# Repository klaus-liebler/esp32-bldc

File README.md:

# esp32-bldc - a bldc controller for stationary applications

* Main components are ESP32-S3, DRV8323HRTAR, 6x IRF7480

* Intgrated synchronous step down converter
* CAN-BUS, RS485 (both with switchable termination)
* USB-C, I2C
* All ceramic capacitors
* Power-LED
* Reset Button, Boot Button
* Thermal sensor
* breakable connector area
* optional MT6816 at the bottom PCB side
* parts available at jlcpcb, (5pcs = 113€)
* various GPIO; especially for external magnetic sensor
* desinged with [KiCad](https://www.kicad.org/) with [https://simplefoc.com/](https://simplefoc.com/) in mind
* Four mounting holes
* dimensions 60mm x 52mm (63mm with big connectors)
* currently COMPLETELY untested

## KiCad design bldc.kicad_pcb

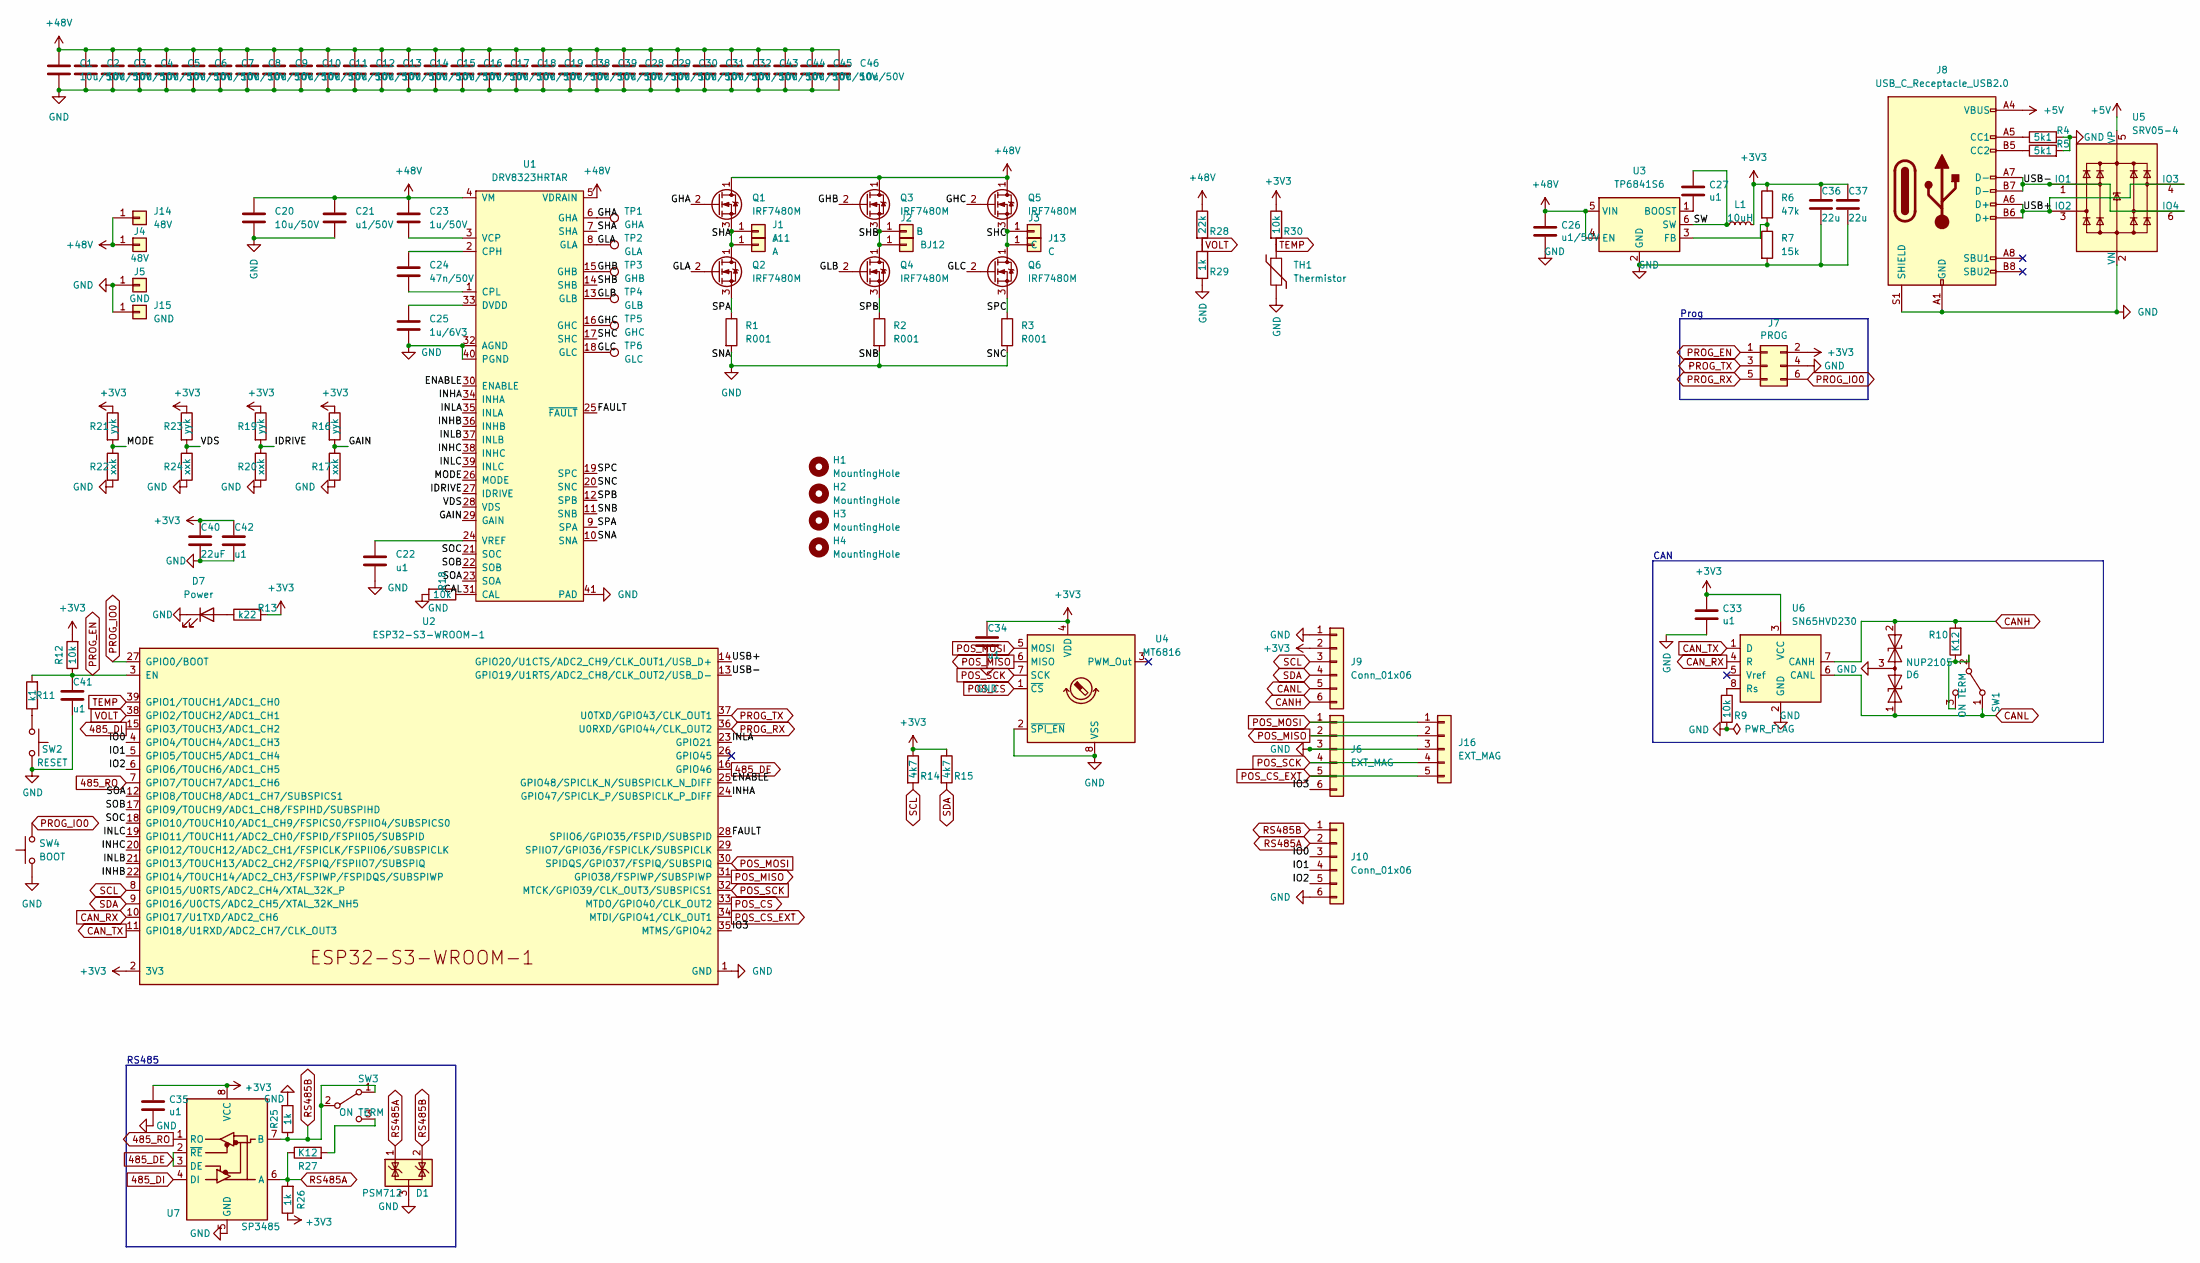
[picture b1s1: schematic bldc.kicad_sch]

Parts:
C1, C2, C3, C4, C5, C6, C7, C8, C9, C10, C11, C12, C13, C14, C15, C16, C17, C18, C19, C28, C29, C30, C31, C32, C38, C39, C43, C44, C45, C46: 10u/50V; C_1206_3216Metric_smaller
C20: 10u/50V; C_1206_3216Metric
C21, C26: u1/50V; C_0603_1608Metric
C22, C27, C33, C35, C41, C42: u1; C_0402_1005Metric
C23: 1u/50V; C_0603_1608Metric
C24: 47n/50V; C_0603_1608Metric
C25: 1u/6V3; C_0402_1005Metric
C34: u1; C_0805_2012Metric_Pad1.18x1.45mm_HandSolder
C36, C37: 22u; C_0603_1608Metric
C40: 22uF; C_0603_1608Metric
D1: PSM712; SOT-23_smaller_withoutSilkscreen
D6: NUP2105; SOT-23_Handsoldering
D7: Power; LED_0603_1608Metric
H1, H2, H3, H4: MountingHole; MountingHole_3.2mm_M3_DIN965
J1: A; SolderWirePad_1x01_SMD_3x5mm
J2: B; SolderWirePad_1x01_SMD_3x5mm
J3: C; SolderWirePad_1x01_SMD_3x5mm
J4: 48V; SolderWirePad_1x01_SMD_3x5mm
J5: GND; SolderWirePad_1x01_SMD_3x5mm
J6: EXT_MAG; JST_XH_S6B-XH-A_1x06_P2.50mm_Horizontal
J7: PROG; IDC_2x03_P1.27mm_Vertical
J8: USB_C_Receptacle_USB2.0; USB_C_Receptacle_HRO_TYPE-C-31-M-12
J9, J10: Conn_01x06; JST_XH_S6B-XH-A_1x06_P2.50mm_Horizontal
J11: A; Steckzunge_4_8mm
J12: B; Steckzunge_4_8mm
J13: C; Steckzunge_4_8mm
J14: 48V; Steckzunge_4_8mm
J15: GND; Steckzunge_4_8mm
J16: EXT_MAG; PhoenixContact_MC_1,5_5-G-3.81_1x05_P3.81mm_Horizontal
L1: 10uH; L_Abracon_ASPI-0630LR
Q1, Q2, Q3, Q4, Q5, Q6: IRF7480M; DirectFET_ME
R1, R2, R3: R001; R_2512_6332Metric
R4, R5: 5k1; R_0402_1005Metric
R6: 47k; R_0402_1005Metric
R7: 15k; R_0402_1005Metric
R9, R12, R18, R30: 10k; R_0402_1005Metric
R10, R27: K12; R_1206_3216Metric_Pad1.30x1.75mm_HandSolder
R11: k1; R_0402_1005Metric
R13: k22; R_0402_1005Metric
R14, R15: 4k7; R_0402_1005Metric
R16, R19, R21, R23: yyk; R_0805_2012Metric_Pad1.20x1.40mm_HandSolder
R17, R20, R22, R24: xxk; R_0805_2012Metric_Pad1.20x1.40mm_HandSolder
R25, R26: 1k; R_0603_1608Metric
R28: 22k; R_0402_1005Metric
R29: 1k; R_0402_1005Metric
SW1, SW3: ON TERM; Switch_SS12D00
SW2: RESET; SW_SPST_TL3342
SW4: BOOT; SW_SPST_TL3342
TH1: Thermistor; R_Axial_DIN0204_L3.6mm_D1.6mm_P1.90mm_Vertical
TP1: GHA; TestPoint_THTPad_D1.0mm_Drill0.5mm
TP2: GLA; TestPoint_THTPad_D1.0mm_Drill0.5mm
TP3: GHB; TestPoint_THTPad_D1.0mm_Drill0.5mm
TP4: GLB; TestPoint_THTPad_D1.0mm_Drill0.5mm
TP5: GHC; TestPoint_THTPad_D1.0mm_Drill0.5mm
TP6: GLC; TestPoint_THTPad_D1.0mm_Drill0.5mm
U1: DRV8323HRTAR; Texas_S-PVQFN-N40_EP4.15x4.15mm_ThermalVias
U2: ESP32-S3-WROOM-1
U3: TP6841S6; TSOT-23-6
U4: MT6816; SO-8_3.9x4.9mm_P1.27mm
U5: SRV05-4; SOT-23-6
U6: SN65HVD230; SOIC-8_3.9x4.9mm_P1.27mm
U7: SP3485; SOIC-8_3.9x4.9mm_P1.27mm

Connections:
485_DE: U2.16 (GPIO46), U7.2 (~RE), U7.3 (DE)
485_DI: U2.15 (GPIO3/TOUCH3/ADC1_CH2), U7.4 (DI)
485_RO: U2.7 (GPIO7/TOUCH7/ADC1_CH6), U7.1 (RO)
+3V3: C33.1, C34.2, C35.2, C36.1, C37.1, C40.1, C42.2, J7.2, J9.2, L1.2, R6.1, R12.2, R13.2, R14.1, R15.1, R16.1, R19.1, R21.1, R23.1, R26.1, R30.1, U2.2 (3V3), U4.4 (VDD), U6.3 (VCC), U7.8 (VCC)
+5V: J8.A4 (VBUS), J8.A9 (VBUS), J8.B4 (VBUS), J8.B9 (VBUS), U5.5 (VP)
+48V: C1.1, C2.1, C3.1, C4.1, C5.1, C6.1, C7.1, C8.1, C9.1, C10.1, C11.1, C12.1, C13.1, C14.1, C15.1, C16.1, C17.1, C18.1, C19.1, C20.2, C21.1, C23.1, C26.1, C28.1, C29.1, C30.1, C31.1, C32.1, C38.1, C39.1, C43.1, C44.1, C45.1, C46.1, J4.1, J14.1, Q1.1 (D), Q3.1 (D), Q5.1 (D), R28.1, U1.4 (VM), U1.5 (VDRAIN), U3.4 (EN), U3.5 (VIN)
/CAL: R18.1, U1.31 (CAL)
/ENABLE: U1.30 (ENABLE), U2.25 (GPIO48/SPICLK_N/SUBSPICLK_N_DIFF)
/FAULT: U1.25 (~FAULT), U2.28 (SPIIO6/GPIO35/FSPID/SUBSPID)
/GAIN: R16.2, R17.1, U1.29 (GAIN)
/GHA: Q1.2 (G), TP1.1, U1.6 (GHA)
/GHB: Q3.2 (G), TP3.1, U1.15 (GHB)
/GHC: Q5.2 (G), TP5.1, U1.16 (GHC)
/GLA: Q2.2 (G), TP2.1, U1.8 (GLA)
/GLB: Q4.2 (G), TP4.1, U1.13 (GLB)
/GLC: Q6.2 (G), TP6.1, U1.18 (GLC)
/IDRIVE: R19.2, R20.1, U1.27 (IDRIVE)
/INHA: U1.34 (INHA), U2.24 (GPIO47/SPICLK_P/SUBSPICLK_P_DIFF)
/INHB: U1.36 (INHB), U2.22 (GPIO14/TOUCH14/ADC2_CH3/FSPIWP/FSPIDQS/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)
/INHC: U1.38 (INHC), U2.20 (GPIO12/TOUCH12/ADC2_CH1/FSPICLK/FSPIIO6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)
/INLA: U1.35 (INLA), U2.23 (GPIO21)
/INLB: U1.37 (INLB), U2.21 (GPIO13/TOUCH13/ADC2_CH2/FSPIQ/FSPIIO7/S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)
/INLC: U1.39 (INLC), U2.19 (GPIO11/TOUCH11/ADC2_CH0/FSPID/FSPIIO5/S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)
/IO0: J10.3, U2.4 (GPIO4/TOUCH4/ADC1_CH3)
/IO1: J10.4, U2.5 (GPIO5/TOUCH5/ADC1_CH4)
/IO2: J10.5, U2.6 (GPIO6/TOUCH6/ADC1_CH5)
/IO3: J6.6, U2.35 (MTMS/GPIO42)
/MODE: R21.2, R22.1, U1.26 (MODE)
/SHA: J1.1, J11.1, Q1.3 (S), Q2.1 (D), U1.7 (SHA)
/SHB: J2.1, J12.1, Q3.3 (S), Q4.1 (D), U1.14 (SHB)
/SHC: J3.1, J13.1, Q5.3 (S), Q6.1 (D), U1.17 (SHC)
/SOA: U1.23 (SOA), U2.12 (GPIO8/TOUCH8/ADC1_CH7/SUBSPICS1)
/SOB: U1.22 (SOB), U2.17 (GPIO9/TOUCH9/ADC1_CH8/FSPIHD/SUBSPIHD)
/SOC: U1.21 (SOC), U2.18 (GPIO10/TOUCH10/ADC1_CH9/FSPICS0/FSPIIO4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)
/SPA: Q2.3 (S), R1.1, U1.9 (SPA)
/SPB: Q4.3 (S), R2.1, U1.12 (SPB)
/SPC: Q6.3 (S), R3.1, U1.19 (SPC)
/SW: C27.1, L1.1, U3.6 (SW)
/USB+: J8.A6 (D+), J8.B6 (D+), U2.14 (GPIO20/U1CTS/ADC2_CH9/CLK_OUT1/USB_D+), U5.3 (IO2), U5.4 (IO3)
/USB-: J8.A7 (D-), J8.B7 (D-), U2.13 (GPIO19/U1RTS/ADC2_CH8/CLK_OUT2/USB_D-), U5.1 (IO1), U5.6 (IO4)
/VDS: R23.2, R24.1, U1.28 (VDS)
CANH: D6.2 (A2), J9.6, R10.2, U6.7 (CANH)
CANL: D6.1 (A1), J9.5, SW1.1 (A), U6.6 (CANL)
CAN_RX: U2.10 (GPIO17/U1TXD/ADC2_CH6), U6.4 (R)
CAN_TX: U2.11 (GPIO18/U1RXD/ADC2_CH7/CLK_OUT3), U6.1 (D)
GND: C1.2, C2.2, C3.2, C4.2, C5.2, C6.2, C7.2, C8.2, C9.2, C10.2, C11.2, C12.2, C13.2, C14.2, C15.2, C16.2, C17.2, C18.2, C19.2, C20.1, C21.2, C22.2, C25.2, C26.2, C28.2, C29.2, C30.2, C31.2, C32.2, C33.2, C34.1, C35.1, C36.2, C37.2, C38.2, C39.2, C40.2, C41.2, C42.1, C43.2, C44.2, C45.2, C46.2, D1.3 (A), D6.3 (common), D7.1 (K), J5.1, J6.3, J7.4, J8.A1 (GND), J8.A12 (GND), J8.B1 (GND), J8.B12 (GND), J8.S1 (SHIELD), J9.1, J10.6, J15.1, J16.3, R1.2, R2.2, R3.2, R4.2, R5.2, R7.2, R9.2, R17.2, R18.2, R20.2, R22.2, R24.2, R25.2, R29.2, SW2.2, SW4.1, TH1.2, U1.10 (SNA), U1.11 (SNB), U1.20 (SNC), U1.32 (AGND), U1.40 (PGND), U1.41 (PAD), U2.1 (GND), U2.40 (GND), U2.41 (GND), U3.2 (GND), U4.2 (~SPI_EN), U4.8 (VSS), U5.2 (VN), U6.2 (GND), U7.5 (GND)
unnamed: C22.1, U1.24 (VREF)
unnamed: C23.2, U1.3 (VCP)
unnamed: C24.1, U1.2 (CPH)
unnamed: C24.2, U1.1 (CPL)
unnamed: C25.1, U1.33 (DVDD)
unnamed: C27.2, U3.1 (BOOST)
unnamed: D7.2 (A), R13.1
unnamed: J8.A5 (CC1), R4.1
unnamed: J8.B5 (CC2), R5.1
unnamed: R6.2, R7.1, U3.3 (FB)
unnamed: R9.1, U6.8 (Rs)
unnamed: R10.1, SW1.2 (B), SW1.3 (C)
unnamed: R11.1, SW2.1
unnamed: R27.2, SW3.3 (C)
POS_CS: U2.33 (MTDO/GPIO40/CLK_OUT2), U4.1 (~CS)
POS_CS_EXT: J6.5, J16.5, U2.34 (MTDI/GPIO41/CLK_OUT1)
POS_MISO: J6.2, J16.2, U2.31 (GPIO38/FSPIWP/SUBSPIWP), U4.6 (MISO)
POS_MOSI: J6.1, J16.1, U2.30 (SPIDQS/GPIO37/FSPIQ/SUBSPIQ), U4.5 (MOSI)
POS_SCK: J6.4, J16.4, U2.32 (MTCK/GPIO39/CLK_OUT3/SUBSPICS1), U4.7 (SCK)
PROG_EN: C41.1, J7.1, R11.2, R12.1, U2.3 (EN)
PROG_IO0: J7.6, SW4.2, U2.27 (GPIO0/BOOT)
PROG_RX: J7.5, U2.36 (U0RXD/GPIO44/CLK_OUT2)
PROG_TX: J7.3, U2.37 (U0TXD/GPIO43/CLK_OUT1)
RS485A: D1.1 (K), J10.2, R26.2, R27.1, U7.6 (A)
RS485B: D1.2 (K), J10.1, R25.1, SW3.1 (A), SW3.2 (B), U7.7 (B)
SCL: J9.3, R14.2, U2.8 (GPIO15/U0RTS/ADC2_CH4/XTAL_32K_P)
SDA: J9.4, R15.2, U2.9 (GPIO16/U0CTS/ADC2_CH5/XTAL_32K_NH5)
TEMP: R30.2, TH1.1, U2.39 (GPIO1/TOUCH1/ADC1_CH0)
VOLT: R28.2, R29.1, U2.38 (GPIO2/TOUCH2/ADC1_CH1)

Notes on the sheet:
RS485
CAN
Prog

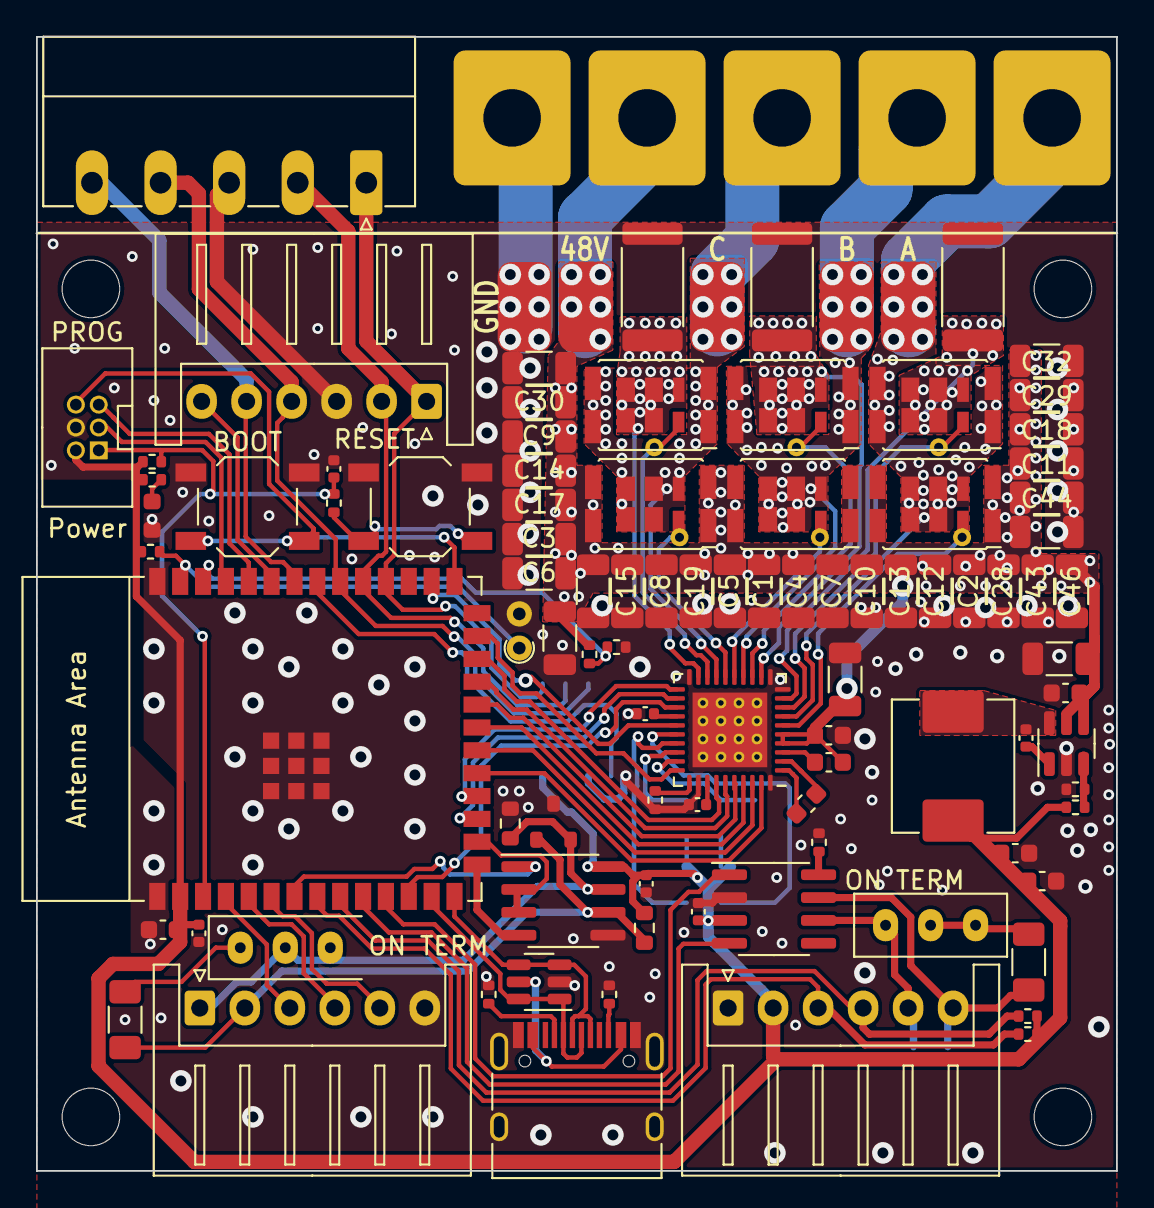
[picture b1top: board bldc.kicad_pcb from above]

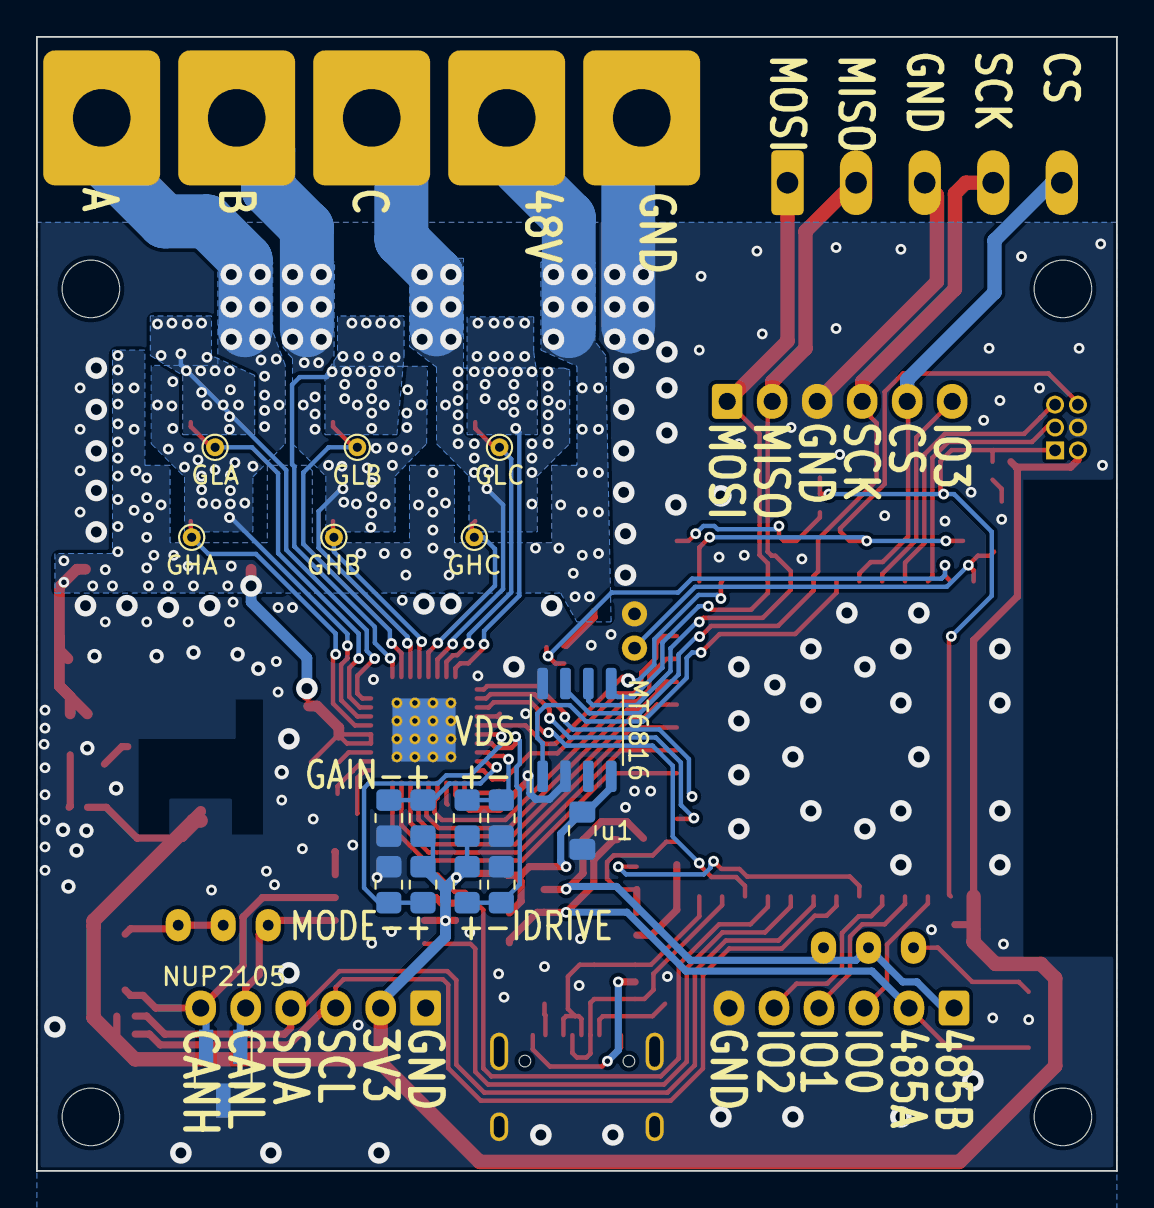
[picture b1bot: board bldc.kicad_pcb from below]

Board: 2 copper layers, 60.0 x 63.0 mm, 123 parts (17 on the bottom side), 75 nets.

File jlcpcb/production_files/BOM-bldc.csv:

Comment,Designator,Footprint,LCSC
1k,R29,R_0402_1005Metric,C11702
SN65HVD230,U6,SOIC-8_3.9x4.9mm_P1.27mm,C12084
10uH,L1,L_Abracon_ASPI-0630LR,C132141
10u/50V,"C1,C10,C11,C12,C13,C14,C15,C16,C17,C18,C19,C2,C20,C28,C29,C3,C30,C31,C32,C38,C4,C5,C6,C7,C8,C9",C_1206_3216Metric,C13585
u1/50V,"C21,C26",C_0603_1608Metric,C14663
IRF7480M,"Q1,Q2,Q3,Q4,Q5,Q6",DirectFET_ME,C152356
u1,"C22,C27,C33,C35,C41,C42",C_0402_1005Metric,C1525
1u/50V,C23,C_0603_1608Metric,C15849
47n/50V,C24,C_0603_1608Metric,C1622
USB_C_Receptacle_USB2.0,J8,USB_C_Receptacle_HRO_TYPE-C-31-M-12,C165948
1k,"R25,R26",R_0603_1608Metric,C21190
Power,D7,LED_0603_1608Metric,C2286
k1,R11,R_0402_1005Metric,C25076
k22,R13,R_0402_1005Metric,C25091
10k,"R12,R18,R30,R9",R_0402_1005Metric,C25744
15k,R7,R_0402_1005Metric,C25756
22k,R28,R_0402_1005Metric,C25768
47k,R6,R_0402_1005Metric,C25792
4k7,"R14,R15",R_0402_1005Metric,C25900
5k1,"R4,R5",R_0402_1005Metric,C25905
TP6841S6,U3,TSOT-23-6,C2844736
ESP32-S3-WROOM-1,U2,ESP32-S3-WROOM-1,C2913199
RESET,"SW2,SW4",SW_SPST_TL3342,C318884
PSM712,D1,SOT-23_smaller_withoutSilkscreen,C32677
1u/6V3,C25,C_0402_1005Metric,C52923
22u,"C36,C37,C40",C_0603_1608Metric,C59461
DRV8323HRTAR,U1,Texas_S-PVQFN-N40_EP4.15x4.15mm_ThermalVias,C701783
R001,"R1,R2,R3",R_2512_6332Metric,C728356
SRV05-4,U5,SOT-23-6,C85364
SP3485,U7,SOIC-8_3.9x4.9mm_P1.27mm,C8963
GND,J15,Steckzunge_4_8mm,
K12,R27,R_1206_3216Metric_Pad1.30x1.75mm_HandSolder,
MountingHole,H2,MountingHole_3.2mm_M3_DIN965,
ON TERM,SW1,Switch_SS12D00,
K12,R10,R_1206_3216Metric_Pad1.30x1.75mm_HandSolder,
PROG,J7,IDC_2x03_P1.27mm_Vertical,
C,J13,Steckzunge_4_8mm,
MountingHole,H4,MountingHole_3.2mm_M3_DIN965,
48V,J14,Steckzunge_4_8mm,
GND,J5,SolderWirePad_1x01_SMD_3x5mm,
EXT_MAG,J16,"PhoenixContact_MC_1,5_5-G-3.81_1x05_P3.81mm_Horizontal",
Thermistor,TH1,R_Axial_DIN0204_L3.6mm_D1.6mm_P1.90mm_Vertical,
MountingHole,H1,MountingHole_3.2mm_M3_DIN965,
MountingHole,H3,MountingHole_3.2mm_M3_DIN965,
ON TERM,SW3,Switch_SS12D00,
EXT_MAG,J6,JST_XH_S6B-XH-A_1x06_P2.50mm_Horizontal,
B,J2,SolderWirePad_1x01_SMD_3x5mm,
A,J11,Steckzunge_4_8mm,
Conn_01x06,J10,JST_XH_S6B-XH-A_1x06_P2.50mm_Horizontal,
B,J12,Steckzunge_4_8mm,
NUP2105,D6,SOT-23_Handsoldering,
C,J3,SolderWirePad_1x01_SMD_3x5mm,
A,J1,SolderWirePad_1x01_SMD_3x5mm,
48V,J4,SolderWirePad_1x01_SMD_3x5mm,
Conn_01x06,J9,JST_XH_S6B-XH-A_1x06_P2.50mm_Horizontal,
xxk,R20,R_0805_2012Metric_Pad1.20x1.40mm_HandSolder,
GHB,TP3,TestPoint_THTPad_D1.0mm_Drill0.5mm,
yyk,R16,R_0805_2012Metric_Pad1.20x1.40mm_HandSolder,
xxk,R22,R_0805_2012Metric_Pad1.20x1.40mm_HandSolder,
GHC,TP5,TestPoint_THTPad_D1.0mm_Drill0.5mm,
xxk,R17,R_0805_2012Metric_Pad1.20x1.40mm_HandSolder,
GHA,TP1,TestPoint_THTPad_D1.0mm_Drill0.5mm,
yyk,R23,R_0805_2012Metric_Pad1.20x1.40mm_HandSolder,
yyk,R19,R_0805_2012Metric_Pad1.20x1.40mm_HandSolder,
xxk,R24,R_0805_2012Metric_Pad1.20x1.40mm_HandSolder,
u1,C34,C_0805_2012Metric_Pad1.18x1.45mm_HandSolder,
GLC,TP6,TestPoint_THTPad_D1.0mm_Drill0.5mm,
GLB,TP4,TestPoint_THTPad_D1.0mm_Drill0.5mm,
MT6816,U4,SO-8_3.9x4.9mm_P1.27mm,
yyk,R21,R_0805_2012Metric_Pad1.20x1.40mm_HandSolder,
GLA,TP2,TestPoint_THTPad_D1.0mm_Drill0.5mm,

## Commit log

2023-02-13 Rendering
